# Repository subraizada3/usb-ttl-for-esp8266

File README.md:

# USB UART TTL for ESP8266

This is a compact CP2102N-based USB Type-C TTL UART breakout board that also includes the DTR and RTS pins needed for button-free programming of the ESP8266.

USB TTL UART adapters available on the market have issues:
- The smaller adapters that have a Type C port don't break out the DTR & RTS pins
- The adapters that do break out DTR & RTS pins also break out a bunch of other unneeded pins, and they're large & bulky. They also have a micro-USB port instead of Type C.

This adapter breaks out all pins needed for efficient ESP8266 development while remaining as compact as possible.

This was created in 2021; the market may have more suitable offerings available at this point.

See [bom.xlsx](bom.xlsx) for the list of parts to order from LCSC or for JLCPCB assembly. [pos.xlsx](pos.xlsx) is the part positioning file for JLCPCB assembly.

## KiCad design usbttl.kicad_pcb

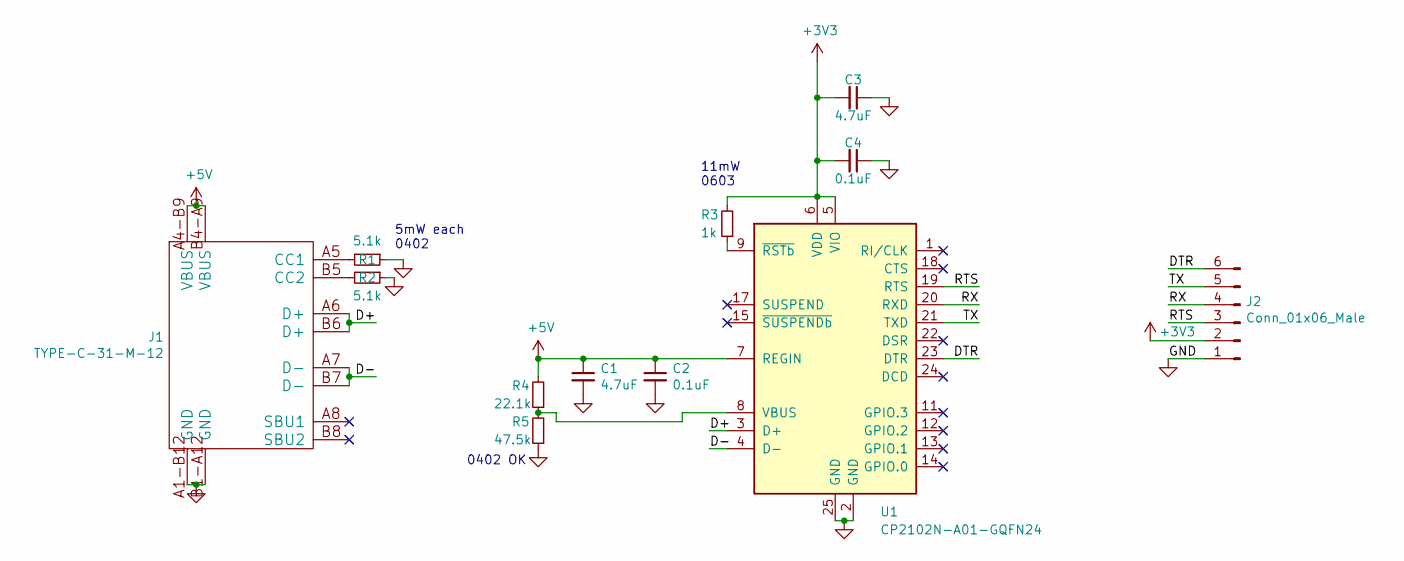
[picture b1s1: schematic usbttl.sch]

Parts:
C1, C3: 4.7uF; C_0402_1005Metric
C2, C4: 0.1uF; C_0402_1005Metric
J1: TYPE-C-31-M-12
J2: Conn_01x06_Male; PinHeader_1x06_P2.54mm_Vertical
R1, R2: 5.1k; R_0402_1005Metric_Pad0.72x0.64mm_HandSolder
R3: 1k; R_0603_1608Metric
R4: 22.1k; R_0402_1005Metric_Pad0.72x0.64mm_HandSolder
R5: 47.5k; R_0402_1005Metric_Pad0.72x0.64mm_HandSolder
U1: CP2102N-A01-GQFN24; QFN-24-1EP_4x4mm_P0.5mm_EP2.6x2.6mm

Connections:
+3V3: C3.2, C4.2, J2.2, R3.2, U1.5 (VIO), U1.6 (VDD)
+5V: C1.1, C2.1, J1.A4-B9 (VBUS), J1.B4-A9 (VBUS), R4.2, U1.7 (REGIN)
/D+: J1.A6 (D+), J1.B6 (D+), U1.3 (D+)
/D-: J1.A7 (D-), J1.B7 (D-), U1.4 (D-)
/DTR: J2.6, U1.23 (DTR)
/RTS: J2.3, U1.19 (RTS)
/RX: J2.4, U1.20 (RXD)
/TX: J2.5, U1.21 (TXD)
GND: C1.2, C2.2, C3.1, C4.1, J1.A1-B12 (GND), J1.B1-A12 (GND), J2.1, R1.1, R2.1, R5.1, U1.2 (GND), U1.25 (GND)
unnamed: J1.A5 (CC1), R1.2
unnamed: J1.B5 (CC2), R2.2
unnamed: R3.1, U1.9 (~RSTb)
unnamed: R4.1, R5.2, U1.8 (VBUS)

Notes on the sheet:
11mW 0603
5mW each 0402
0402 OK

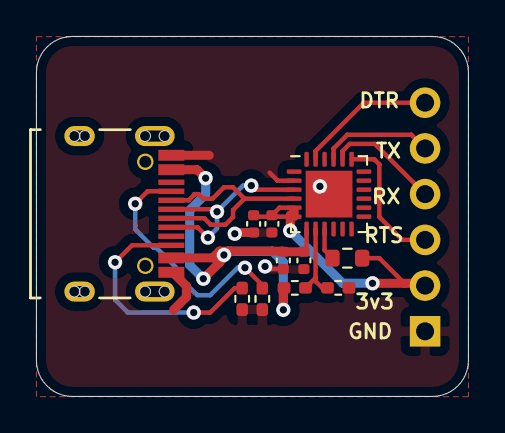
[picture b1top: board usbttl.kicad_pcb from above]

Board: 2 copper layers, 24.0 x 20.0 mm, 12 parts (0 on the bottom side), 13 nets.

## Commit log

2024-12-19 track project
